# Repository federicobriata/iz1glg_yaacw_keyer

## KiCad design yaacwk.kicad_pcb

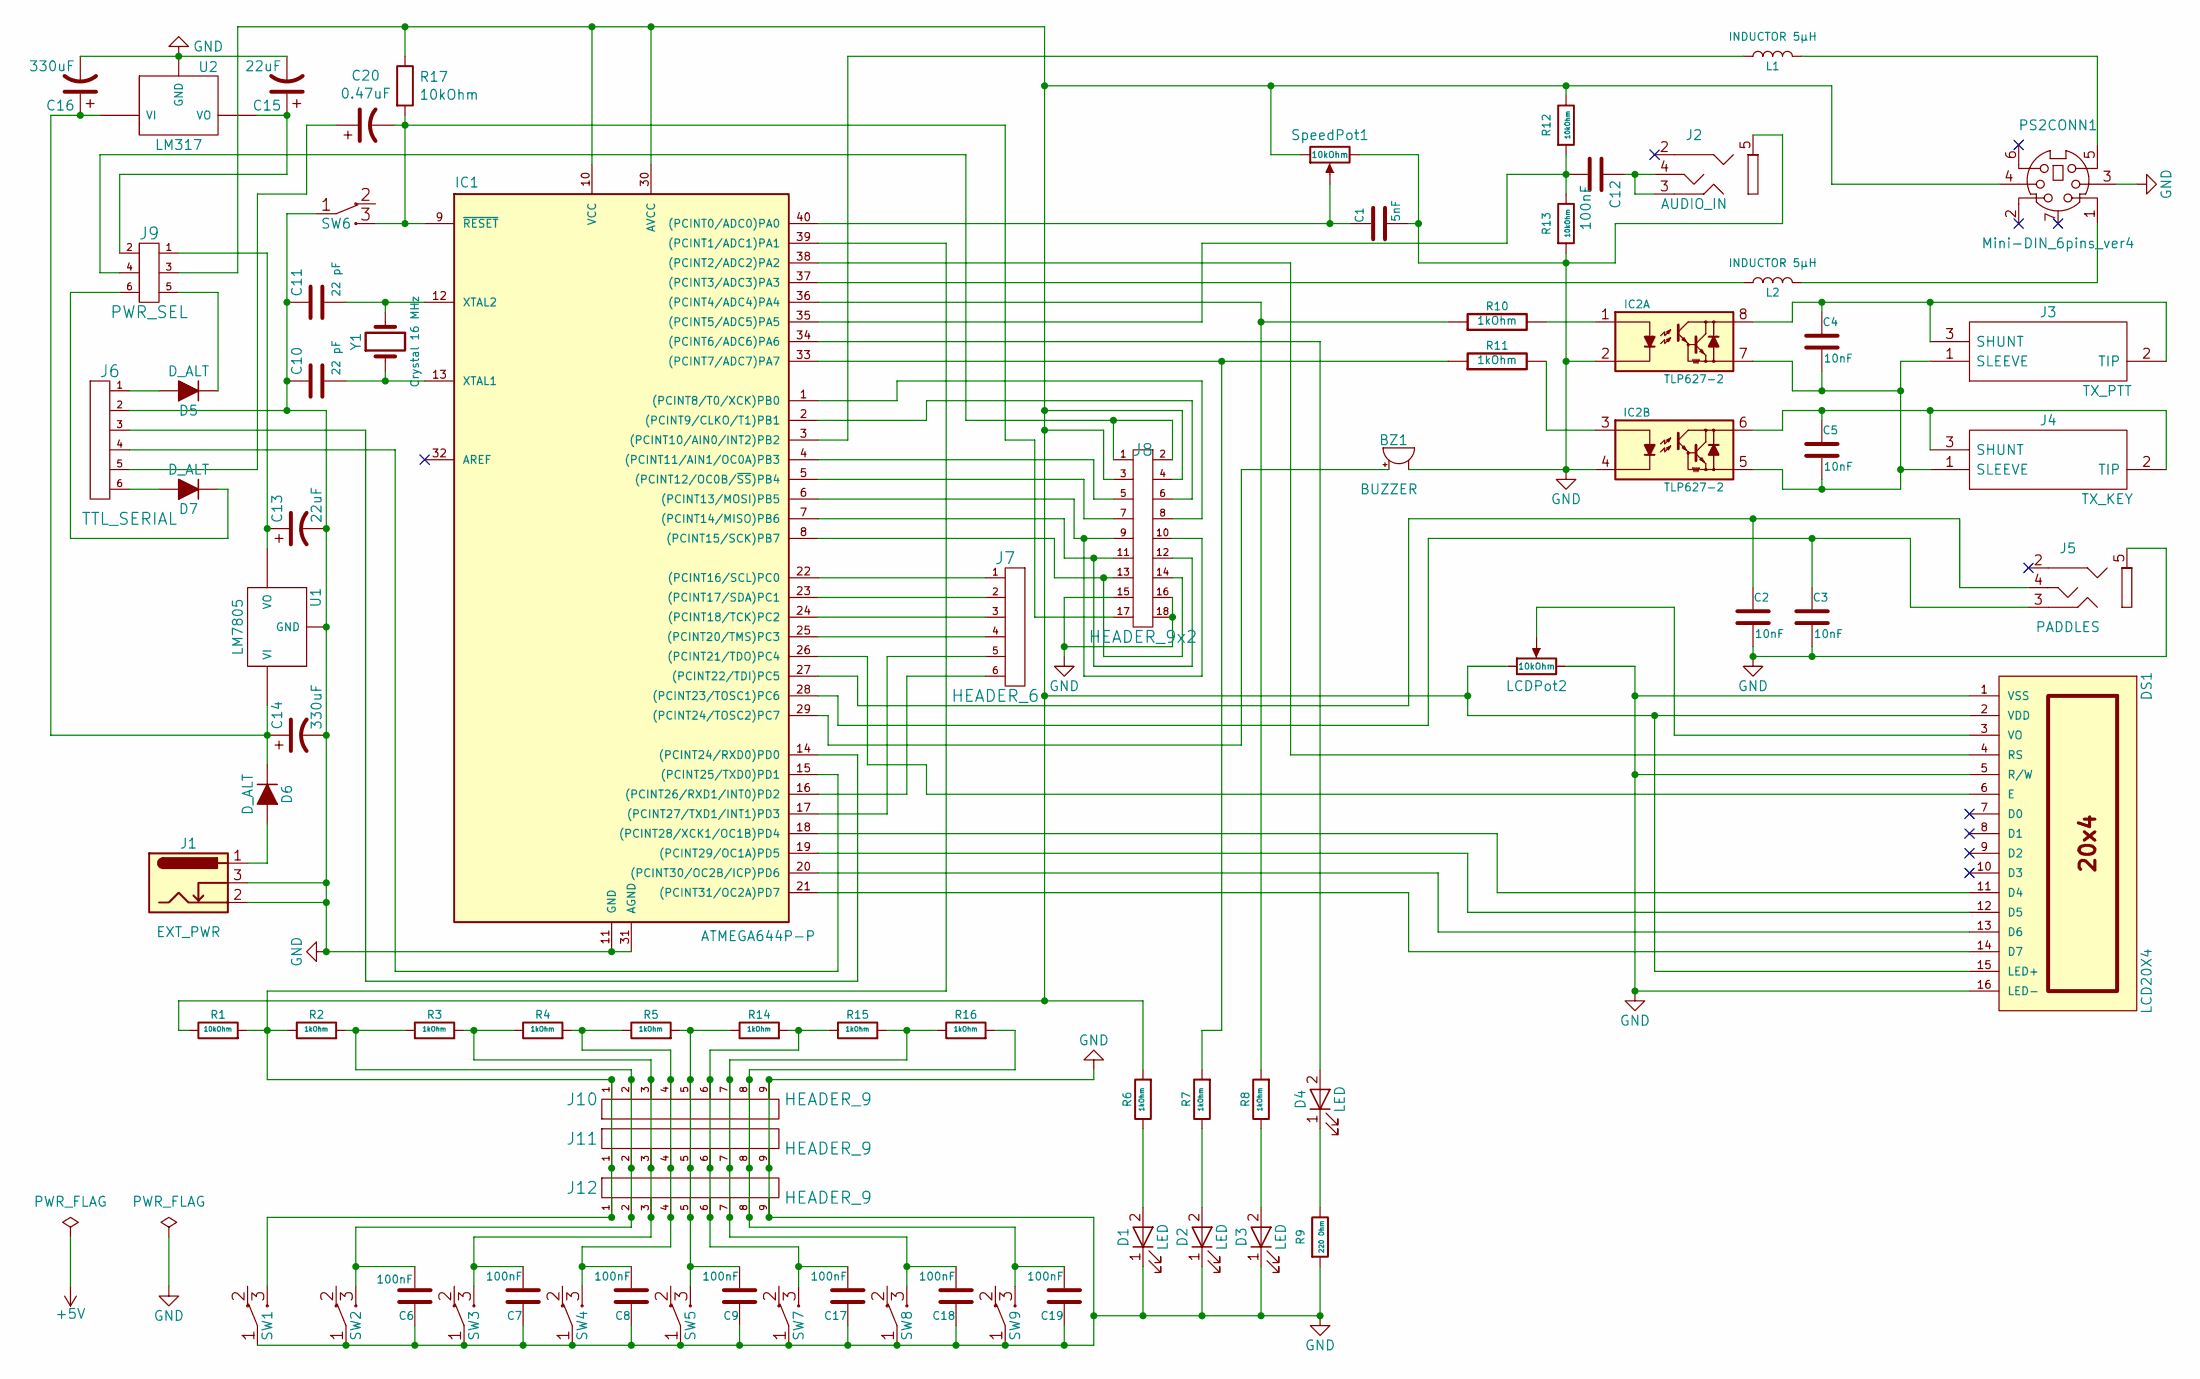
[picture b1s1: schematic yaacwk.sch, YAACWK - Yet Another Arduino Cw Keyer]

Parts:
BZ1: BUZZER; Buzzer_12x9.5RM7.6
C1: 5nF; C_Disc_D3.0mm_W1.6mm_P2.50mm
C2, C3, C4, C5: 10nF; C_Disc_D3.0mm_W1.6mm_P2.50mm
C6, C7, C8, C9, C17, C18, C19: 100nF; C_Disc_D3.4mm_W2.1mm_P2.50mm
C10, C11: 22 pF; C_Disc_D3.0mm_W1.6mm_P2.50mm
C12: 100nF; C_Disc_D3.8mm_W2.6mm_P2.50mm
C13, C15: 22uF; CP_Radial_D5.0mm_P2.50mm
C14, C16: 330uF; CP_Radial_D8.0mm_P3.80mm
C20: 0.47uF; CP_Radial_D5.0mm_P2.50mm
D1, D2, D3: LED; LED_D3.0mm
D4: LED; LED_D4.0mm
D5, D6, D7: D_ALT; D_A-405_P7.62mm_Horizontal
DS1: LCD20X4; Pin_Header_Straight_1x16_Pitch2.54mm
IC1: ATMEGA644P-P; DIP-40_W15.24mm
IC2: TLP627-2; DIP-8_W7.62mm
J1: EXT_PWR; BARREL_JACK
J2: AUDIO_IN; PJ320A_3.5mm_4_conductors_audio_plug
J3: TX_PTT; PJRAN1X1U03AUX; Manufacturer_Part_Number PJRAN1X1U03AUX; Mouser Part Number 502-PJRAN1X1U03AUX
J4: TX_KEY; PJRAN1X1U03AUX; Manufacturer_Part_Number PJRAN1X1U03AUX; Mouser Part Number 502-PJRAN1X1U03AUX
J5: PADDLES; PJ320A_3.5mm_4_conductors_audio_plug
J6: TTL_SERIAL; Pin_Header_Straight_1x06_Pitch2.54mm
J7: HEADER_6; Pin_Header_Straight_1x06_Pitch2.54mm
J8: HEADER_9x2; Pin_Header_Straight_2x09_Pitch2.54mm
J9: PWR_SEL; Pin_Header_Straight_2x03_Pitch2.54mm
J10, J11, J12: HEADER_9; Pin_Header_Straight_1x09_Pitch2.54mm
L1, L2: INDUCTOR 5μH; L_Axial_L7.0mm_D3.3mm_P10.16mm_Horizontal_Fastron_MICC
LCDPot2: 10kOhm; Potentiometer_Trimmer_ACP_CA9h5_Vertical_Px5.0mm_Py5.0mm
PS2CONN1: Mini-DIN_6pins_ver4; Mini_din6
R1, R12, R13, R17: 10kOhm; R_Axial_DIN0207_L6.3mm_D2.5mm_P7.62mm_Horizontal
R2, R3, R4, R5, R6, R7, R8, R10, R11, R14, R15, R16: 1kOhm; R_Axial_DIN0207_L6.3mm_D2.5mm_P7.62mm_Horizontal
R9: 220 Ohm; R_Axial_DIN0207_L6.3mm_D2.5mm_P7.62mm_Horizontal
SW1, SW2, SW3, SW4, SW5, SW6, SW7, SW8, SW9: SW_SPDT; SW_TH_Tactile_Omron_B3F-10xx
SpeedPot1: 10kOhm; Potentiometer_Piher_T16H_Single_Vertical
U1: LM7805; 78XX
U2: LM317; 78XX
Y1: Crystal 16 MHz; Crystal_HC49-U_Vertical

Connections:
GND: BZ1.2, C1.2, C2.2, C3.2, C6.1, C7.1, C8.1, C9.1, C10.1, C11.1, C13.2, C14.2, C15.2, C16.2, C17.1, C18.1, C19.1, D1.1 (K), D2.1 (K), D3.1 (K), DS1.1 (VSS), DS1.5 (R/W), DS1.16 (LED-), IC1.11 (GND), IC1.31 (AGND), IC2.2, IC2.4, J1.2, J1.3, J2.5 (GND), J5.5 (GND), J6.2, J8.15, J8.16, J8.18, J10.9, J11.9, J12.9, LCDPot2.3, PS2CONN1.3, R9.2, R13.2, SW1.1 (COM), SW2.1 (COM), SW3.1 (COM), SW4.1 (COM), SW5.1 (COM), SW6.1 (COM), SW7.1 (COM), SW8.1 (COM), SW9.1 (COM), SpeedPot1.3, U1.GND, U2.GND; also elsewhere on the board
unnamed: BZ1.1, IC1.29 ((PCINT24/TOSC2)PC7)
unnamed: C1.1, IC1.40 ((PCINT0/ADC0)PA0), SpeedPot1.2
unnamed: C2.1, IC1.27 ((PCINT22/TDI)PC5), J5.4 (R)
unnamed: C3.1, IC1.28 ((PCINT23/TOSC1)PC6), J5.3 (L)
unnamed: C4.1, IC2.8, J3.2 (TIP), J3.3 (SHUNT)
unnamed: C4.2, C5.2, IC2.5, IC2.7, J3.1 (SLEEVE), J4.1 (SLEEVE)
unnamed: C5.1, IC2.6, J4.2 (TIP), J4.3 (SHUNT)
unnamed: C6.2, J10.2, J11.2, J12.2, R2.2, R3.1, SW2.3 (NO)
unnamed: C7.2, J10.3, J11.3, J12.3, R3.2, R4.1, SW3.3 (NO)
unnamed: C8.2, J10.4, J11.4, J12.4, R4.2, R5.1, SW4.3 (NO)
unnamed: C9.2, J10.5, J11.5, J12.5, R5.2, R14.1, SW5.3 (NO)
unnamed: C10.2, IC1.13 (XTAL1), Y1.1
unnamed: C11.2, IC1.12 (XTAL2), Y1.2
unnamed: C12.1, J2.3 (L), J2.4 (R)
unnamed: C12.2, IC1.35 ((PCINT5/ADC5)PA5), R12.2, R13.1
unnamed: C13.1, J9.1, U1.VO
unnamed: C14.1, C16.1, D6.1 (K), U1.VI, U2.VI
unnamed: C15.1, J9.2, U2.VO
unnamed: C17.2, J10.6, J11.6, J12.6, R14.2, R15.1, SW7.3 (NO)
unnamed: C18.2, J10.7, J11.7, J12.7, R15.2, R16.1, SW8.3 (NO)
unnamed: C19.2, J10.8, J11.8, J12.8, R16.2, SW9.3 (NO)
unnamed: C20.1, J6.5
unnamed: C20.2, IC1.9 (~RESET), J8.17, R17.2, SW6.3 (NO)
unnamed: D1.2 (A), R6.1
unnamed: D2.2 (A), R7.1
unnamed: D3.2 (A), R8.1
unnamed: D4.1 (K), R9.1
unnamed: D4.2 (A), IC1.34 ((PCINT6/ADC6)PA6)
unnamed: D5.1 (K), J9.5
unnamed: D5.2 (A), J6.1
unnamed: D6.2 (A), J1.1
unnamed: D7.1 (K), J9.6
unnamed: D7.2 (A), J6.6
unnamed: DS1.3 (VO), LCDPot2.2
unnamed: DS1.4 (RS), IC1.38 ((PCINT2/ADC2)PA2)
unnamed: DS1.6 (E), IC1.26 ((PCINT21/TDO)PC4)
unnamed: DS1.11 (D4), IC1.18 ((PCINT28/XCK1/OC1B)PD4)
unnamed: DS1.12 (D5), IC1.19 ((PCINT29/OC1A)PD5)
unnamed: DS1.13 (D6), IC1.20 ((PCINT30/OC2B/ICP)PD6)
unnamed: DS1.14 (D7), IC1.21 ((PCINT31/OC2A)PD7)
unnamed: DS1.2 (VDD), DS1.15 (LED+), IC1.10 (VCC), IC1.30 (AVCC), J8.3, J8.4, J9.3, LCDPot2.1, PS2CONN1.4, R1.1, R6.2, R12.1, R17.1, SpeedPot1.1
unnamed: IC1.1 ((PCINT8/T0/XCK)PB0), J8.8
unnamed: IC1.2 ((PCINT9/CLKO/T1)PB1), J8.6
unnamed: IC1.3 ((PCINT10/AIN0/INT2)PB2), L1.1
unnamed: IC1.4 ((PCINT11/AIN1/OC0A)PB3), J8.5
unnamed: IC1.5 ((PCINT12/OC0B/~SS~)PB4), J8.7
unnamed: IC1.6 ((PCINT13/MOSI)PB5), J8.9, J8.10
unnamed: IC1.7 ((PCINT14/MISO)PB6), J8.11, J8.12
unnamed: IC1.8 ((PCINT15/SCK)PB7), J8.13, J8.14
unnamed: IC1.14 ((PCINT24/RXD0)PD0), J6.3
unnamed: IC1.15 ((PCINT25/TXD0)PD1), J6.4
unnamed: IC1.16 ((PCINT26/RXD1/INT0)PD2), J7.6
unnamed: IC1.17 ((PCINT27/TXD1/INT1)PD3), J7.5
unnamed: IC1.22 ((PCINT16/SCL)PC0), J7.1
unnamed: IC1.23 ((PCINT17/SDA)PC1), J7.2
unnamed: IC1.24 ((PCINT18/TCK)PC2), J7.3
unnamed: IC1.25 ((PCINT20/TMS)PC3), J7.4
unnamed: IC1.33 ((PCINT7/ADC7)PA7), R7.2, R11.1
unnamed: IC1.36 ((PCINT4/ADC4)PA4), R8.2, R10.1
unnamed: IC1.37 ((PCINT3/ADC3)PA3), L2.1
unnamed: IC1.39 ((PCINT1/ADC1)PA1), J10.1, J11.1, J12.1, R1.2, R2.1, SW1.3 (NO)
unnamed: IC2.1, R10.2
unnamed: IC2.3, R11.2
unnamed: J8.1, J8.2, J9.4
unnamed: L1.2, PS2CONN1.5
unnamed: L2.2, PS2CONN1.1

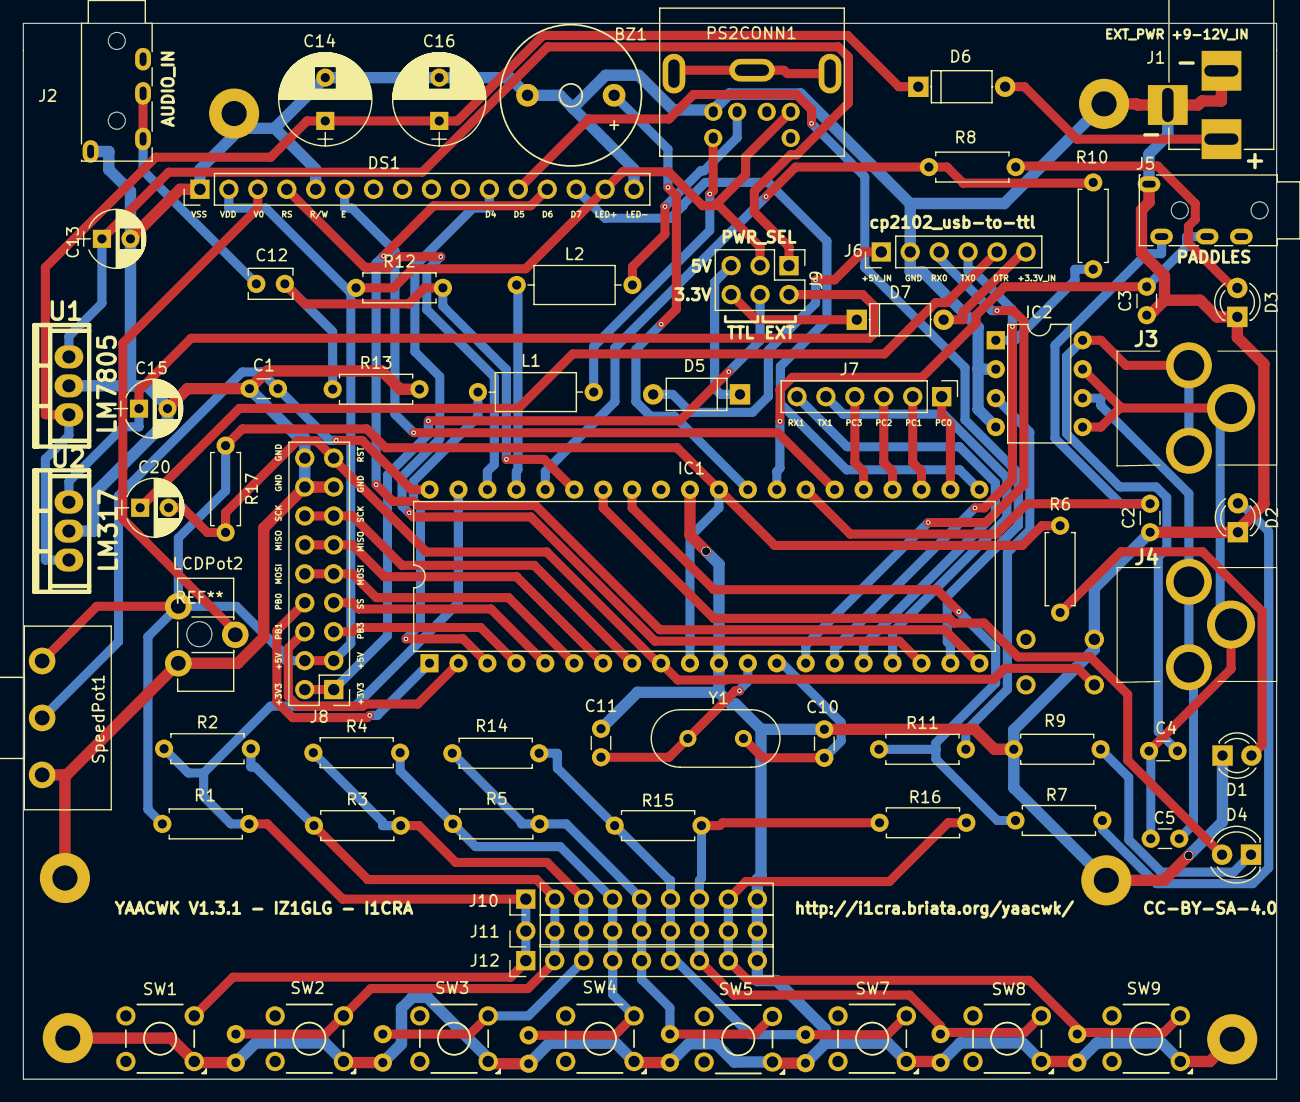
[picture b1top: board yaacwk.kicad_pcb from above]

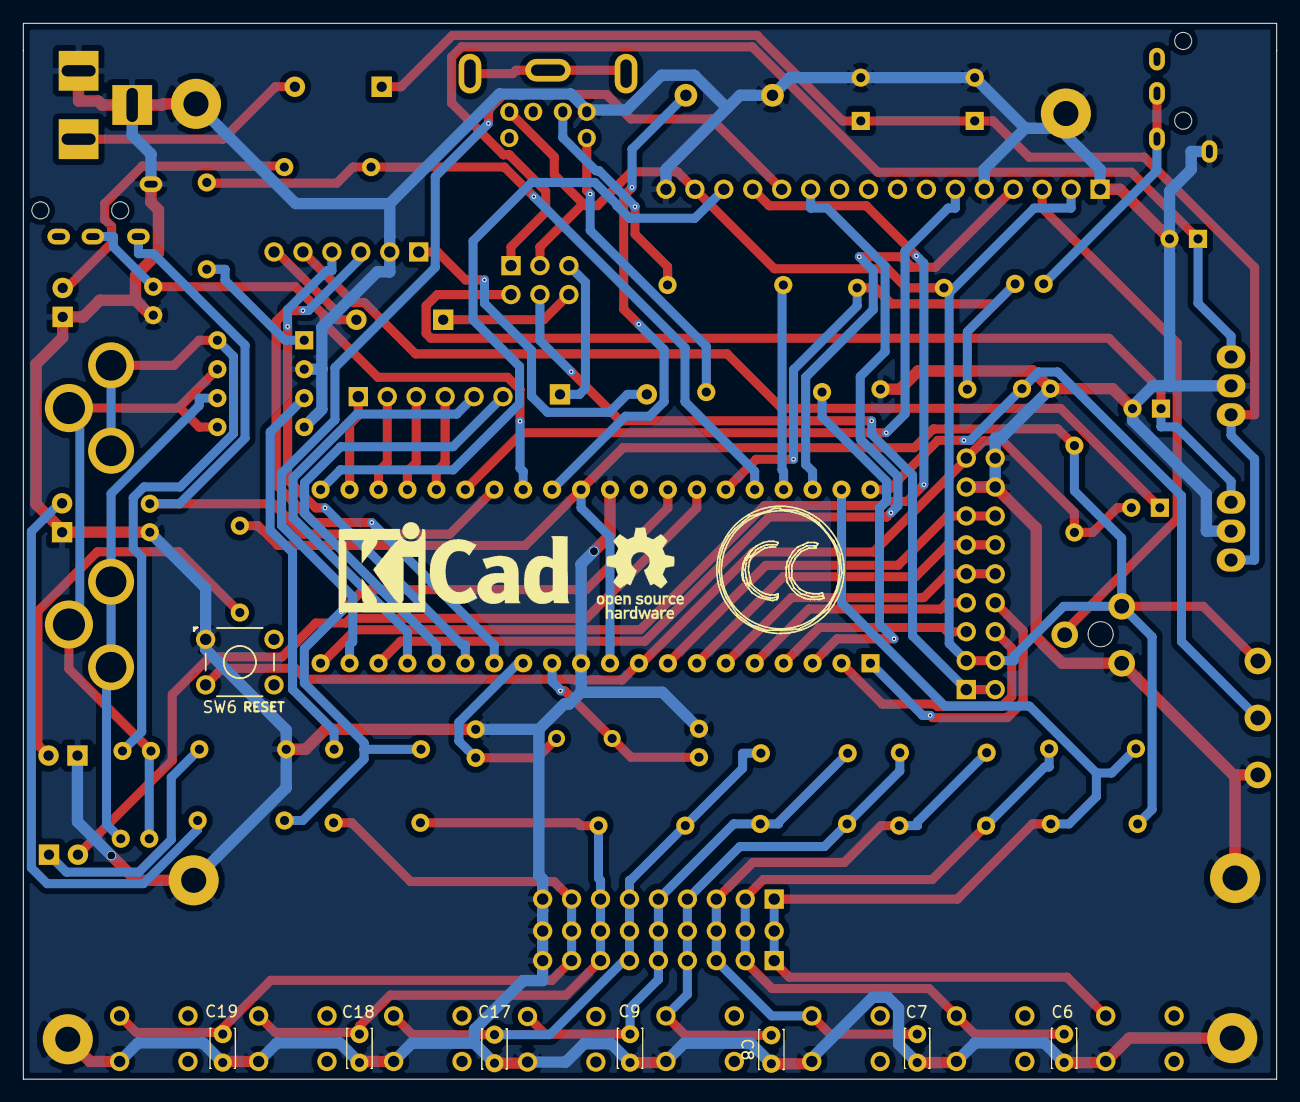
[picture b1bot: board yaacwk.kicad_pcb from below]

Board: 2 copper layers, 110.0 x 92.7 mm, 86 parts (11 on the bottom side), 67 nets.

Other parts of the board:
HOLE1, HOLE2, HOLE3, HOLE4, HOLE5, HOLE6: MountingHole_2.2mm_M2_Pad
REF1: KiCad-Logo_8mm_SilkScreen
REF2: OSHW-Logo_7.5x8mm_SilkScreen
REF3: Symbol_CreativeCommons_SilkScreenTop_Type2_Big

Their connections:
GND: HOLE1.1, HOLE2.1, HOLE3.1, HOLE4.1, HOLE5.1, HOLE6.1; also elsewhere on the board

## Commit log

2018-07-09 Add YAACWK KiCad Schematic Sources for Arduino Nano v3
2018-07-09 Add YAACWK KiCad Schematic Sources for AtMega 644p
2018-07-09 Updated YAACWK Kicad to allign with latest pin settings for AtMega 644p variant
    moved ps2_keyboard_clock to pin2 (pin3 on AtMega 644p is not an interrupt capable pin!)
    moved paddle_left to pin3
    added cw decoder indicator LED on pin30
2018-07-09 fix eechema, cw_decored reenabled and speed pot now is working
2018-07-09 fix yaawck eeschema for display, to reflect the current src code
2018-07-09 yaacwk, eeschema cleanup, ps2 pinout fixed, uart ttl and new power input added
2018-07-09 yaacwk, pcb v1, netlist polulated, component placed
2018-07-09 yaacwk, fix kicad lib
2018-07-09 changing library to prepare dependency for pcb v1.1
2018-07-09 modified kicad library mini_din6
2018-07-09 new kicad library audio stereo jack: PJ320A
2018-07-09 yaacwk pcb v1.1_RC updated eechema
2018-07-09 removed kicad and yaacwk_atmega_644p folder
2018-07-09 removed yaacwk_atmega_644p folder also from kicad project files
2018-07-09 adding License
2018-07-10 fix library path
2018-07-10 upgrade eeschema version
2019-02-11 add gerber for yaacwk v1.1
2019-02-11 Yaacwk v1.2 with gerber
2021-02-15 Yaacwk v1.3 with gerber and current WIP
2021-03-03 cosmetic fix
2021-03-03 fix eeschema yaacwk v1.3, old file was double plotted. thanks Jürgen DK8AP for let me know about this problem

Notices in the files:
kicad/yaacwk_atmega_644p/yaacwk.sch:
Copyright: CC BY-SA 3.0 IT by: I1cra - Iz1glg
yaacwk.kicad_pcb:
Copyright: CC BY-SA 4.0 by: Iz1glg - I1cra
YAACWK V1.3.1 - IZ1GLG - I1CRA http://i1cra.briata.org/yaacwk/ CC-BY-SA-4.0
